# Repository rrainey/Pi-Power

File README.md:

# Pi-Power for DSKY-matic

This is an integrated power supply for the DSKY-matic.  It supplies 5VDC for the
Raspberry Pi, keyboard, and alarm modules. It also supplies either +3.3VDC or +7VDC for the Display module, depending on whether you are using the LED or EL variant of that module.

Takes power from a 9-24VDC power adapter. I am testing the DSKY-matic using a TRIAD model WS8U090-2000; 7VDC 2.0A.

PCB based on the original Pi-Power project from Tonymac32. I added a separate +3.3 VDC section to the original +5 VDC-only design.

## A Warning from the original author

Do not stick your fingers into this circuit while it's powering 
something you care about.  
Your fingers have a resistance value, and will change the feedback network regulating the output circuit, potentially 
causing a power surge.

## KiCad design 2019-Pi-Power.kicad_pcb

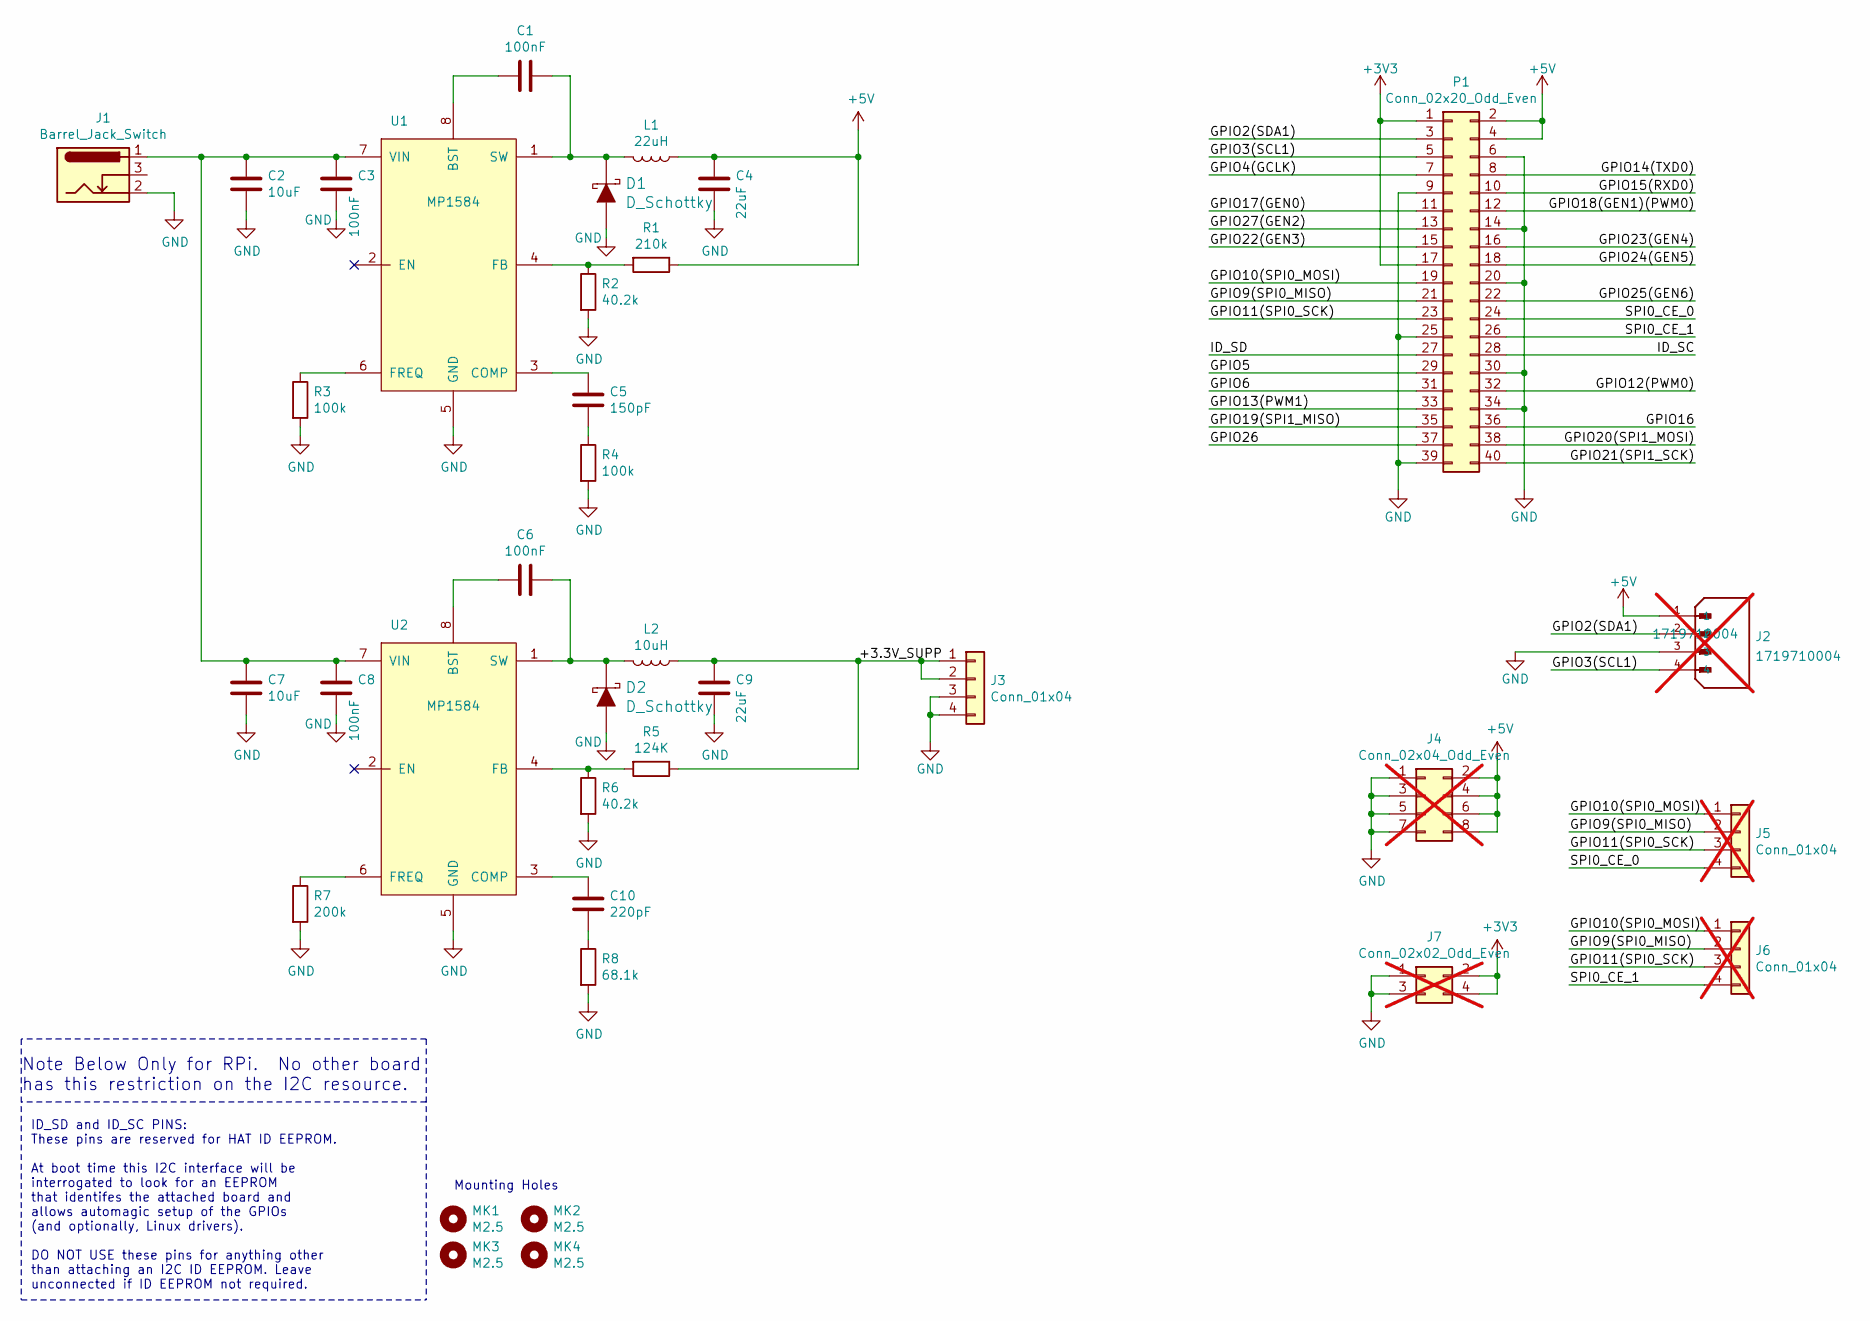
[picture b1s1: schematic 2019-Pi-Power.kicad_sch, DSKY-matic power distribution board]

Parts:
C1, C3, C6, C8: 100nF; C_0603_1608Metric; MPN CL10B104KB8NNNC
C2, C7: 10uF; C_Elec_6.3x5.8; MPN EEE-1HA100SP
C4, C9: 22uF; C_Elec_6.3x5.8; MPN EEH-ZA1H220P
C5: 150pF; C_0603; MPN CL10B151KB8NNNC
C10: 220pF; C_0603_1608Metric; MPN CL10B221KB8NFNC
D1, D2: D_Schottky; DO-214AC; MPN B340A-13-F
J1: Barrel_Jack_Switch; BARREL_JACK; MPN PJ-002AH
J2: 1719710004; MOLEX_1719710004; PARTREV C1; not fitted
J3: Conn_01x04; PinHeader_1x04_P2.54mm_Vertical
J4: Conn_02x04_Odd_Even; Pin_Header_Straight_2x04_Pitch2.54mm; not fitted
J5, J6: Conn_01x04; Pin_Header_Straight_1x04_Pitch2.54mm; not fitted
J7: Conn_02x02_Odd_Even; Pin_Header_Straight_2x02_Pitch2.54mm; not fitted
L1: 22uH; L_10.4x10.4_H4.8; MPN 7447714220
L2: 10uH; L_10.4x10.4_H4.8; MPN 744065100
MK1, MK2, MK3, MK4: M2.5; MountingHole_2.7mm_M2.5
P1: Conn_02x20_Odd_Even; PinSocket_2x20_P2.54mm_Vertical
R1: 210k; R_0603_1608Metric; MPN ERJ-H3EF2103V
R2, R6: 40.2k; R_0603_1608Metric; MPN ERA-3VEB4022V
R3, R4: 100k; R_0603_1608Metric; MPN ERJ-H3EF1003V
R5: 124K; R_0603_1608Metric; MPN RN73R1JTTD1243D25
R7: 200k; R_0603_1608Metric; MPN ERJ-H3EF2003V
R8: 68.1k; R_0603_1608Metric; MPN MCT06030C6812FP500
U1, U2: MP1584; SO-8_5.3x6.2mm_P1.27mm; MPN MP1584EN-LF-Z

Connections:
+3V3: J7.2, J7.4, P1.1, P1.17
+5V: C4.1, J2.1, J4.2, J4.4, J4.6, J4.8, L1.1, P1.2, P1.4, R1.1
/+3.3V_SUPP: C9.1, J3.1, J3.2, L2.1, R5.1
/GPIO2(SDA1): J2.2, P1.3
/GPIO3(SCL1): J2.4, P1.5
/GPIO4(GCLK): P1.7
/GPIO5: P1.29
/GPIO6: P1.31
/GPIO9(SPI0_MISO): J5.2, J6.2, P1.21
/GPIO10(SPI0_MOSI): J5.1, J6.1, P1.19
/GPIO11(SPI0_SCK): J5.3, J6.3, P1.23
/GPIO12(PWM0): P1.32
/GPIO13(PWM1): P1.33
/GPIO14(TXD0): P1.8
/GPIO15(RXD0): P1.10
/GPIO16: P1.36
/GPIO17(GEN0): P1.11
/GPIO18(GEN1)(PWM0): P1.12
/GPIO19(SPI1_MISO): P1.35
/GPIO20(SPI1_MOSI): P1.38
/GPIO21(SPI1_SCK): P1.40
/GPIO22(GEN3): P1.15
/GPIO23(GEN4): P1.16
/GPIO24(GEN5): P1.18
/GPIO25(GEN6): P1.22
/GPIO26: P1.37
/GPIO27(GEN2): P1.13
/ID_SC: P1.28
/ID_SD: P1.27
/SPI0_CE_0: J5.4, P1.24
/SPI0_CE_1: J6.4, P1.26
GND: C2.2, C3.2, C4.2, C7.2, C8.2, C9.2, D1.A, D2.A, J1.2, J2.3, J3.3, J3.4, J4.1, J4.3, J4.5, J4.7, J7.1, J7.3, P1.6, P1.9, P1.14, P1.20, P1.25, P1.30, P1.34, P1.39, R2.2, R3.2, R4.2, R6.2, R7.2, R8.2, U1.5 (GND), U2.5 (GND)
unnamed: C5.2, R4.1
unnamed: C10.2, R8.1
unnamed: C1.2, U1.8 (BST)
unnamed: C5.1, U1.3 (COMP)
unnamed: R1.2, R2.1, U1.4 (FB)
unnamed: R3.1, U1.6 (FREQ)
unnamed: C1.1, D1.K, L1.2, U1.1 (SW)
unnamed: C2.1, C3.1, C7.1, C8.1, J1.1, U1.7 (VIN), U2.7 (VIN)
unnamed: C6.2, U2.8 (BST)
unnamed: C10.1, U2.3 (COMP)
unnamed: R5.2, R6.1, U2.4 (FB)
unnamed: R7.1, U2.6 (FREQ)
unnamed: C6.1, D2.K, L2.2, U2.1 (SW)

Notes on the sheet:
Mounting Holes
Note Below Only for RPi. No other board has this restriction on the I2C resource.
ID_SD and ID_SC PINS: These pins are reserved for HAT ID EEPROM. At boot time this I2C interface will be interrogated to look for an EEPROM that identifes the attached board and allows automagic setup of the GPIOs (and optionally, Linux drivers). DO NOT USE these pins for anything other than attach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

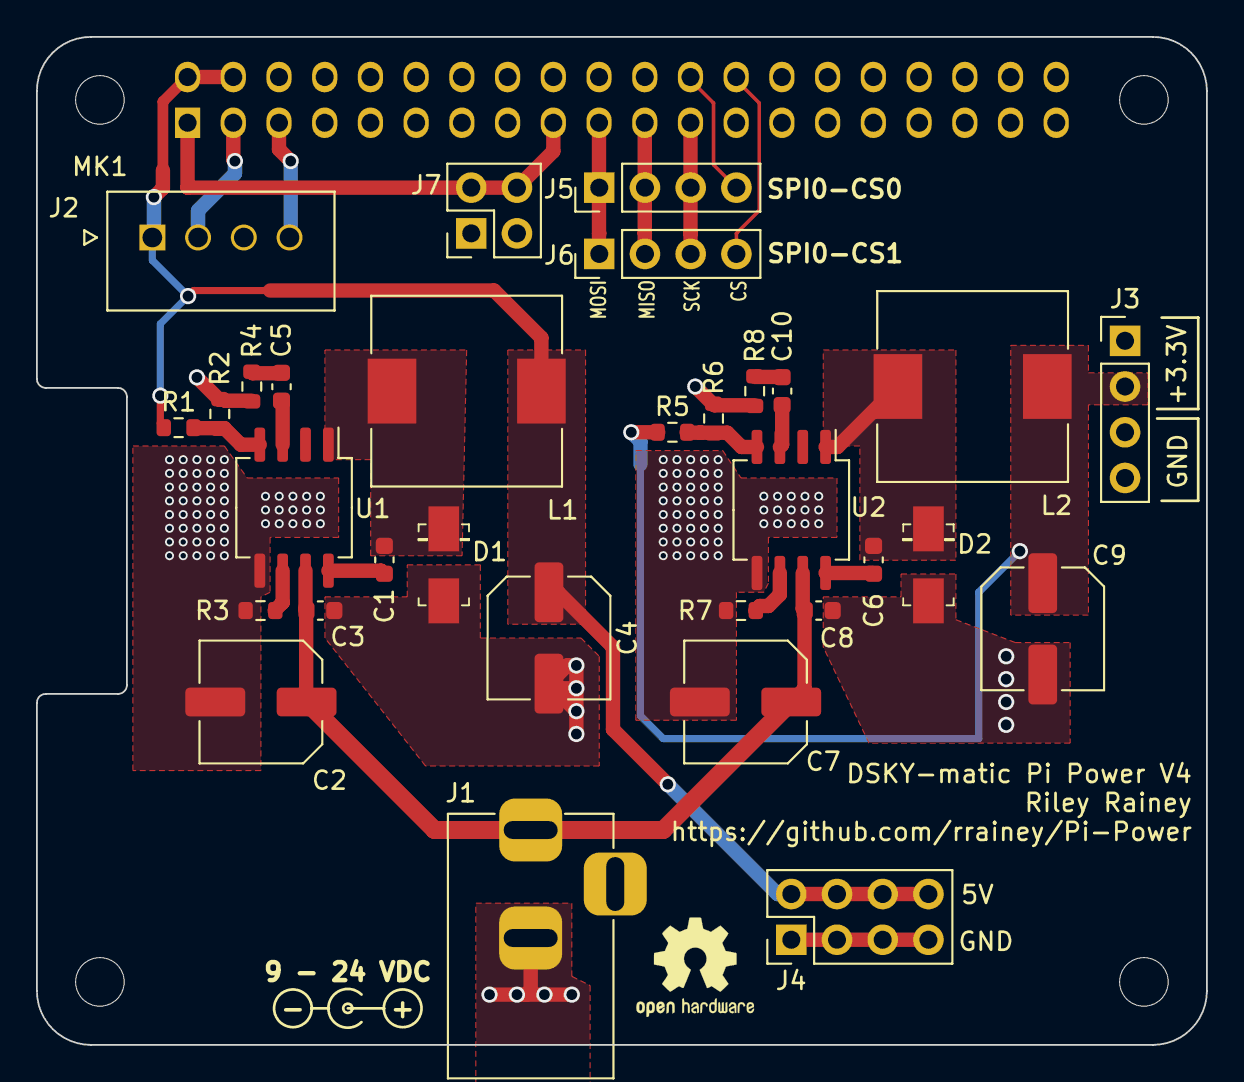
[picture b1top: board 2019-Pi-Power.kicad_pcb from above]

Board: 2 copper layers, 65.0 x 56.0 mm, 36 parts (1 on the bottom side), 24 nets.

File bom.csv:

Reference, Quantity, Value, Footprint, Datasheet
C1 C3 C6 C8 ,4,"100nF","Capacitor_SMD:C_0603_1608Metric","~"
C10 ,1,"220pF","Capacitor_SMD:C_0603_1608Metric","~"
C2 C7 ,2,"10uF","Capacitor_SMD:C_Elec_6.3x5.8","~"
C4 C9 ,2,"22uF","Capacitor_SMD:C_Elec_6.3x5.8","~"
C5 ,1,"150pF","Capacitors_SMD:C_0603","~"
D1 D2 ,2,"D_Schottky","digikey-footprints:DO-214AC","~"
J1 ,1,"Barrel_Jack_Switch","Connectors:BARREL_JACK","~"
J3 J2 ,2,"Conn_01x04","Connector_PinHeader_2.54mm:PinHeader_1x04_P2.54mm_Vertical","~"
J4 ,1,"Conn_02x04_Odd_Even","Pin_Headers:Pin_Header_Straight_2x04_Pitch2.54mm","~"
J5 J6 ,2,"Conn_01x04","Pin_Headers:Pin_Header_Straight_1x04_Pitch2.54mm","~"
J7 ,1,"Conn_02x02_Odd_Even","Pin_Headers:Pin_Header_Straight_2x02_Pitch2.54mm","~"
L1 ,1,"22uH","Inductor_SMD:L_10.4x10.4_H4.8","~"
L2 ,1,"10uH","Inductor_SMD:L_10.4x10.4_H4.8","~"
MK1 MK2 MK3 MK4 ,4,"M2.5","MountingHole:MountingHole_2.7mm_M2.5",""
P1 ,1,"Conn_02x20_Odd_Even","Connector_PinSocket_2.54mm:PinSocket_2x20_P2.54mm_Vertical",""
R1 ,1,"210k","Resistor_SMD:R_0603_1608Metric","~"
R2 R6 ,2,"40.2k","Resistor_SMD:R_0603_1608Metric","~"
R4 R3 ,2,"100k","Resistor_SMD:R_0603_1608Metric","~"
R5 ,1,"124K","Resistor_SMD:R_0603_1608Metric","~"
R7 ,1,"200k","Resistor_SMD:R_0603_1608Metric","~"
R8 ,1,"68.1k","Resistor_SMD:R_0603_1608Metric","~"
U1 U2 ,2,"MP1584","Package_SO:SO-8_5.3x6.2mm_P1.27mm",""

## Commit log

2021-09-11 V1 of DSKY-matic variant of this board
2021-10-10 V2 board: fix issue with + power input on back of board
2021-10-10 Update README to describe TRIAD power supply
2021-10-10 Added change description in the README
2023-02-18 ignore backup files
2023-02-19 V3 Board - adds Molex I2C interconnect
2025-04-01 V4 PCB
